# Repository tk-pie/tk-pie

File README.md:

# Tk🥧
Alternatively: **tk-pie**, or **Test Keyboard Please IgnorE**.
A split keyboard design and firmware.

## Directory

### `/lib`
A rust library, and the bulk of the keyboard firmware implementation.
Written using the Embassy framework.

### `/left` and `/right`
Rust binaries, one for each half of the split keyboard.
Most of the actual logic is implemented in `/lib`.

### `/schematic`
KiCad schematics of the keyboard PCBs.

### `/case`
3d-printable files of the keyboard case and related plastics.

### `/editor`
A graphical program for configuring the keyboard layout. Work in progress.

## Compilation target

This Rust workspace contains crates which should be compiled for different targets.
When developing firmware, the target should be set to e.g. `riscv32imac-unknown-none-elf`:

    cargo check --target riscv32imac-unknown-none-elf

And when developing for desktop, the target should be set to your host target.
By default, this is the case. The target can be configured in your editor, or in
`.cargo/config.toml`

## Firmware development

Required tools:
- Rust
- `probe-rs` for flashing the firmware. Follow instructions at https://probe.rs/
- [`flip-link`](https://github.com/knurling-rs/flip-link/)
- A debug probe of some kind, I recommend a [Pitaya-Link](https://github.com/makerdiary/pitaya-link)

To flash:
- plug in the probe,
- `cd` into either `left` or `right`
- `cargo run`

### Running tests
The keyboad library comes with some unit tests:
```
cargo test -p tk-pie --target x86_64-unknown-linux-gnu
```

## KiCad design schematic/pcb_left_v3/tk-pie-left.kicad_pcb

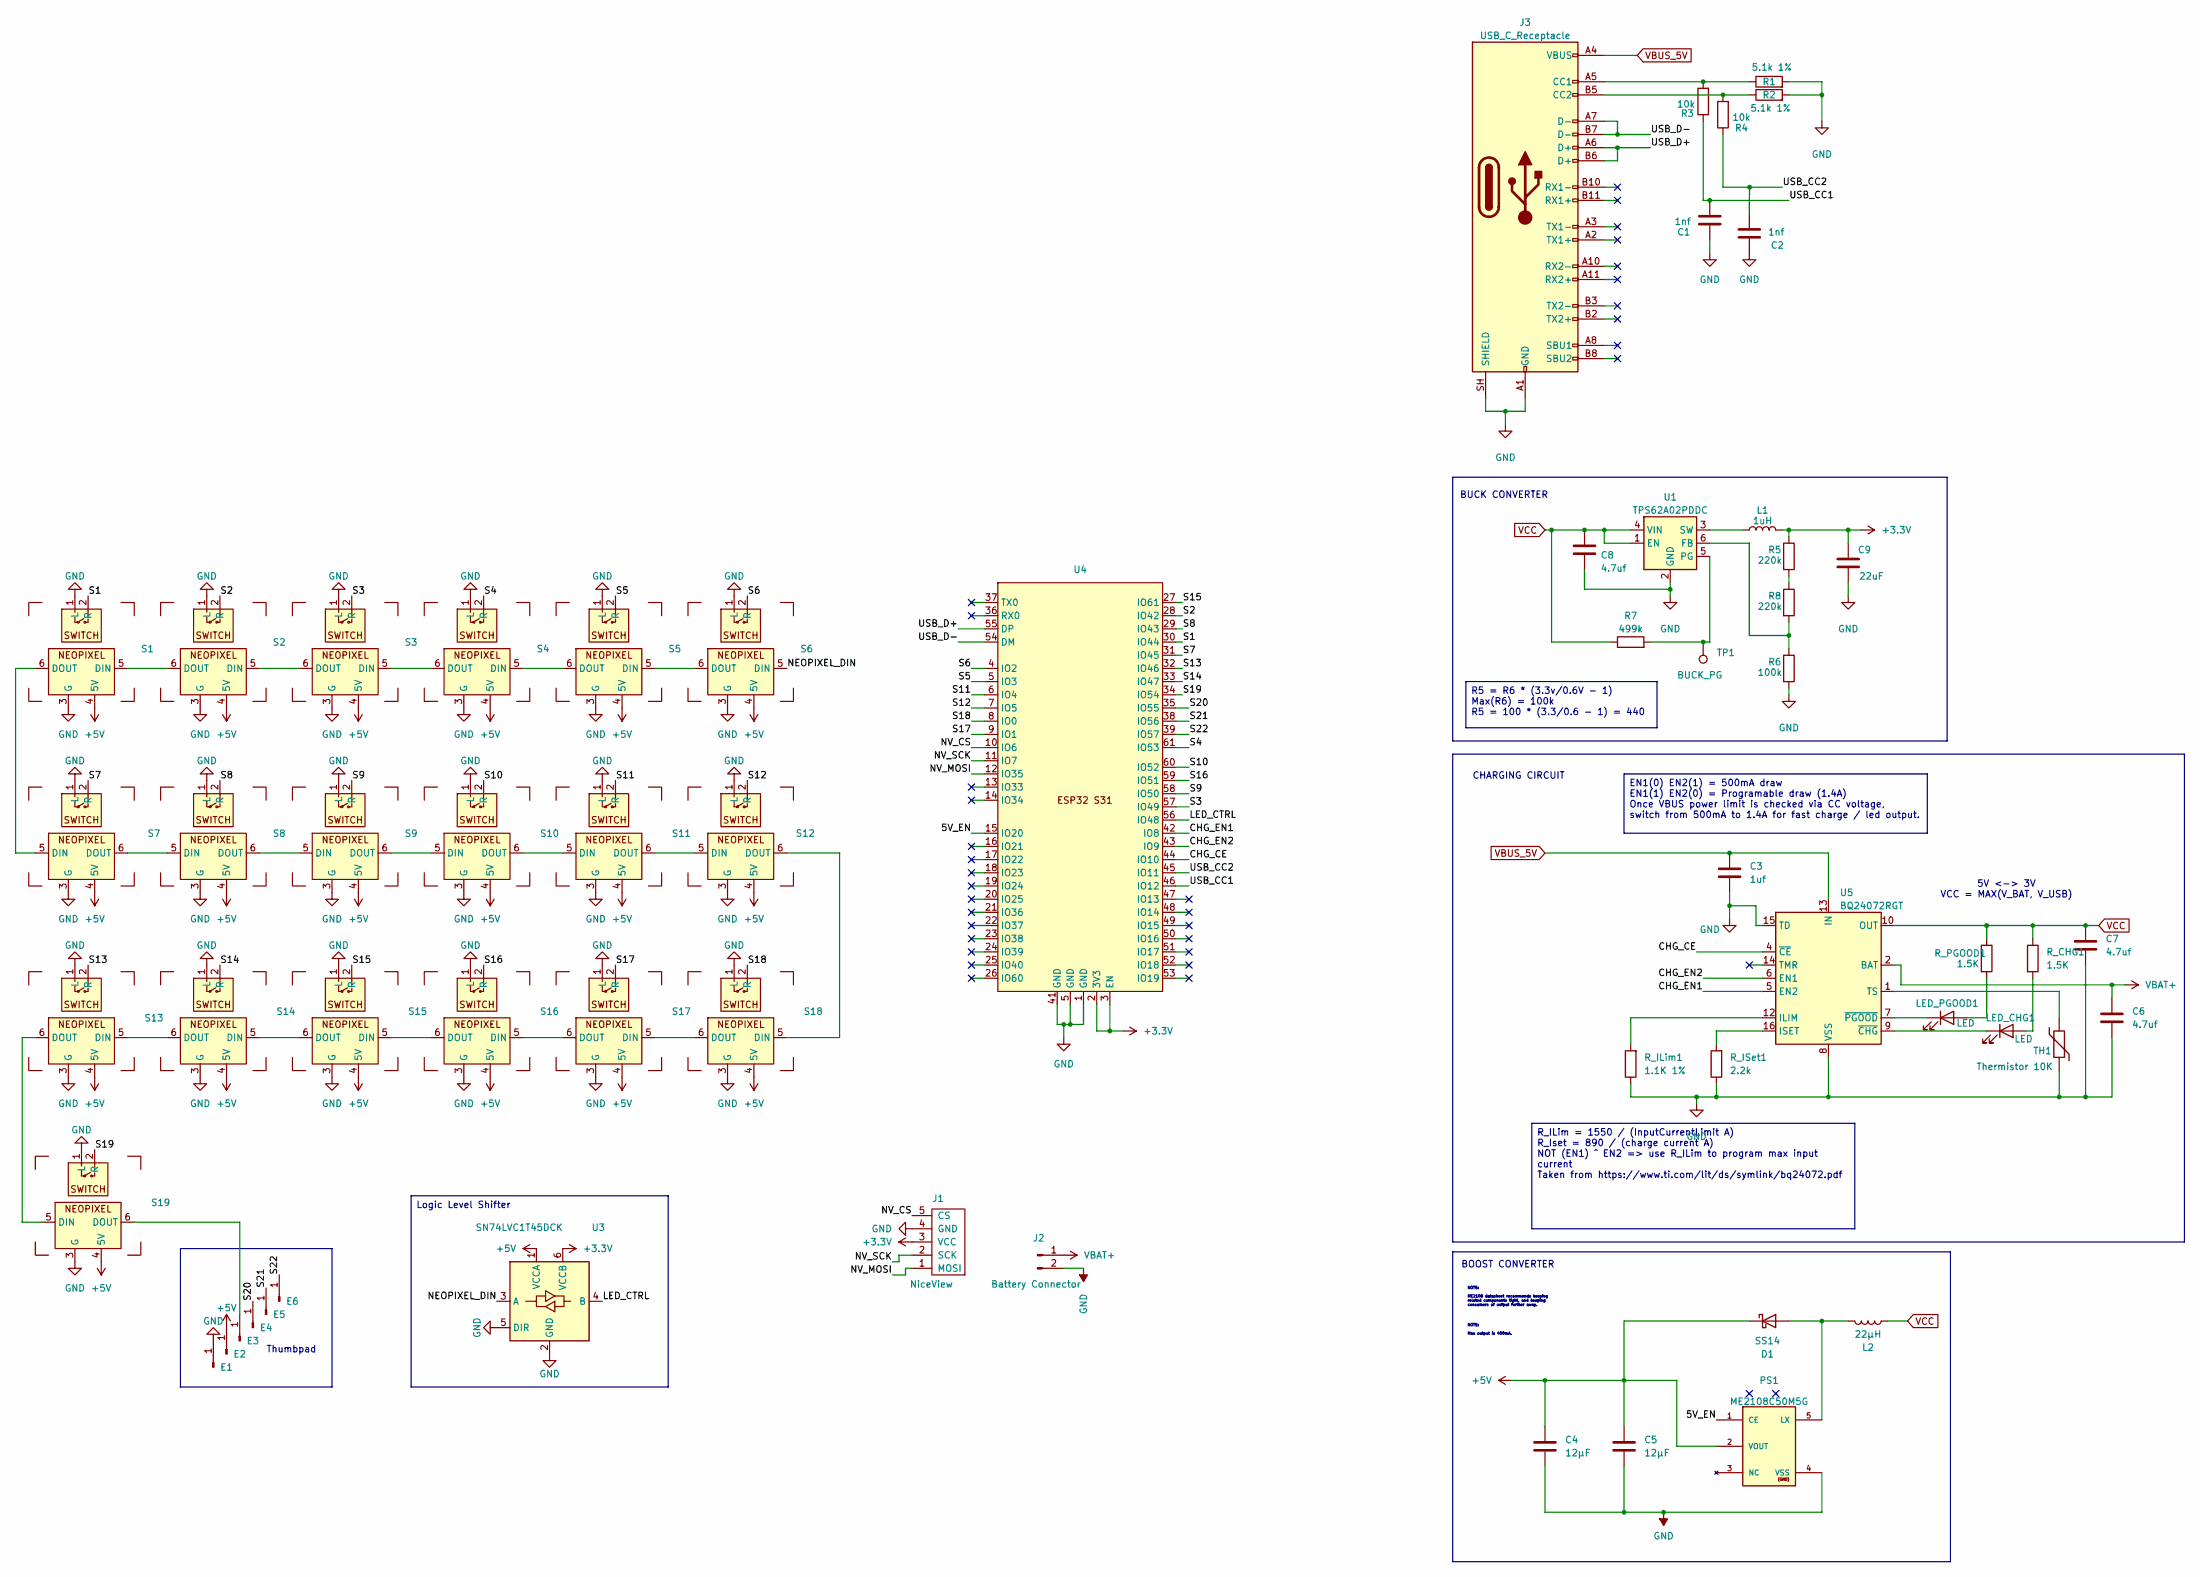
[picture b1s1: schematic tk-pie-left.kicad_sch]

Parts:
C1, C2: 1nf; C_0402_1005Metric_Pad0.74x0.62mm_HandSolder
C3: 1uf; C_0402_1005Metric_Pad0.74x0.62mm_HandSolder
C4, C5: 12µF; C_1210_3225Metric_Pad1.33x2.70mm_HandSolder
C6, C7, C8: 4.7uf; C_0402_1005Metric
C9: 22uF; C_1206_3216Metric
D1: SS14; D_SMA
E1, E2, E3, E4, E5, E6: Conn_01x01_Pin; Pin0.9mm
J1: NiceView; Nice!View Header
J2: Battery Connector; JST_PH_S2B-PH-SM4-TB_1x02-1MP_P2.00mm_Horizontal
J3: USB_C_Receptacle; USB_C_Receptacle_Molex_105450-0101
L1: 1uH; L_1008_2520Metric
L2: 22µH; L_Cenker_CKCS5040
LED_CHG1: LED; LED_0603_1608Metric
LED_PGOOD1: LED; LED_0603_1608Metric
PS1: ME2108C50M5G; SOT-23-5
R1, R2: 5.1k 1%; R_0402_1005Metric
R3, R4: 10k; R_0402_1005Metric
R5, R8: 220k; R_0402_1005Metric
R6: 100k; R_0402_1005Metric
R7: 499k; R_0402_1005Metric
R_CHG1: 1.5K; R_0402_1005Metric
R_ILim1: 1.1K 1%; R_0402_1005Metric
R_ISet1: 2.2k; R_0402_1005Metric
R_PGOOD1: 1.5K; R_0402_1005Metric
S1, S4, S5, S6, S13: MX_SW_SOCKET_LED
S2, S3, S14, S15, S16, S17, S18: MX_SW_SOCKET_LED
S7, S8, S9, S10, S11, S12, S19: MX_SW_SOCKET_RGB_REV; MX_SW_SOCKET_LED_REV
TH1: Thermistor 10K; PinHeader_1x02_P2.54mm_Vertical
TP1: BUCK_PG; TestPoint_Pad_2.5x2.5mm
U1: TPS62A02PDDC; SOT-23-6
U3: SN74LVC1T45DCK; SOT-363_SC-70-6_Handsoldering
U4: ESP32-S31-WROOM-1
U5: BQ24072RGT; VQFN-16-1EP_3x3mm_P0.5mm_EP1.6x1.6mm

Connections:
+3.3V: C9.1, J1.3 (VCC), L1.2, R5.1, U3.6 (VCCB), U4.2 (3V3), U4.3 (EN)
+5V: C4.1, C5.2, D1.1 (K), E2.1 (Pin_1_1), PS1.2 (VOUT), S1.4 (5V), S2.4 (5V), S3.4 (5V), S4.4 (5V), S5.4 (5V), S6.4 (5V), S7.4 (5V), S8.4 (5V), S9.4 (5V), S10.4 (5V), S11.4 (5V), S12.4 (5V), S13.4 (5V), S14.4 (5V), S15.4 (5V), S16.4 (5V), S17.4 (5V), S18.4 (5V), S19.4 (5V), U3.1 (VCCA)
/5V_EN: PS1.1 (CE), U4.15 (IO20)
/ NV_CS: J1.5 (CS), U4.10 (IO6)
/CHG_CE: U4.44 (IO10), U5.4 (~CE)
/CHG_EN1: U4.42 (IO8), U5.5 (EN2)
/CHG_EN2: U4.43 (IO9), U5.6 (EN1)
/LED_CTRL: U3.4 (B), U4.56 (IO48)
/NEOPIXEL_DIN: S6.5 (DIN), U3.3 (A)
/NV_MOSI: J1.1 (MOSI), U4.12 (IO35)
/NV_SCK: J1.2 (SCK), U4.11 (IO7)
/S1: S1.2 (R), U4.30 (IO44)
/S2: S2.2 (R), U4.28 (IO42)
/S3: S3.2 (R), U4.57 (IO49)
/S4: S4.2 (R), U4.61 (IO53)
/S6: S6.2 (R), U4.4 (IO2)
/S7: S7.2 (R), U4.31 (IO45)
/S8: S8.2 (R), U4.29 (IO43)
/S9: S9.2 (R), U4.58 (IO50)
/S10: S10.2 (R), U4.60 (IO52)
/S11: S11.2 (R), U4.6 (IO4)
/S12: S12.2 (R), U4.7 (IO5)
/S13: S13.2 (R), U4.32 (IO46)
/S14: S14.2 (R), U4.33 (IO47)
/S15: S15.2 (R), U4.27 (IO61)
/S16: S16.2 (R), U4.59 (IO51)
/S17: S17.2 (R), U4.9 (IO1)
/S18: S18.2 (R), U4.8 (IO0)
/S19: S19.2 (R), U4.34 (IO54)
/S20: E4.1 (Pin_1_1), U4.35 (IO55)
/S21: E5.1 (Pin_1_1), U4.38 (IO56)
/S22: E6.1 (Pin_1_1), U4.39 (IO57)
/USB_CC1: C1.1, R3.1, U4.46 (IO12)
/USB_CC2: C2.1, R4.1, U4.45 (IO11)
/USB_D+: J3.A6 (D+), J3.B6 (D+), U4.55 (DP)
/USB_D-: J3.A7 (D-), J3.B7 (D-), U4.54 (DM)
unnamed: D1.2 (A), L2.2, PS1.5 (LX)
unnamed: E3.1 (Pin_1_1), S19.6 (DOUT)
unnamed: J3.A5 (CC1), R1.1, R3.2
unnamed: J3.B5 (CC2), R2.1, R4.2
unnamed 40: LED_CHG1.2 (A), R_CHG1.2; also elsewhere on the board
unnamed 41: LED_CHG1.1 (K), U5.9 (~CHG); also elsewhere on the board
unnamed 42: LED_PGOOD1.2 (A), R_PGOOD1.2; also elsewhere on the board
unnamed 43: LED_PGOOD1.1 (K), U5.7 (~PGOOD); also elsewhere on the board
unnamed: R5.2, R8.1
unnamed: S1.5 (DIN), S2.6 (DOUT)
unnamed: S1.6 (DOUT), S7.5 (DIN)
unnamed: S2.5 (DIN), S3.6 (DOUT)
unnamed: S3.5 (DIN), S4.6 (DOUT)
unnamed: S4.5 (DIN), S5.6 (DOUT)
unnamed: S5.5 (DIN), S6.6 (DOUT)
unnamed: S7.6 (DOUT), S8.5 (DIN)
unnamed: S8.6 (DOUT), S9.5 (DIN)
unnamed: S9.6 (DOUT), S10.5 (DIN)
unnamed: S10.6 (DOUT), S11.5 (DIN)
unnamed: S11.6 (DOUT), S12.5 (DIN)
unnamed: S12.6 (DOUT), S18.5 (DIN)
unnamed: S13.5 (DIN), S14.6 (DOUT)
unnamed: S13.6 (DOUT), S19.5 (DIN)
unnamed: S14.5 (DIN), S15.6 (DOUT)
unnamed: S15.5 (DIN), S16.6 (DOUT)
unnamed: S16.5 (DIN), S17.6 (DOUT)
unnamed: S17.5 (DIN), S18.6 (DOUT)
unnamed: R6.1, R8.2, U1.6 (FB)
unnamed: R7.2, TP1.1, U1.5 (PG)
unnamed: L1.1, U1.3 (SW)
unnamed: R_ILim1.2, U5.12 (ILIM)
unnamed: R_ISet1.2, U5.16 (ISET)
unnamed: TH1.2, U5.1 (TS)
VBAT+: C6.1, J2.1, U5.2 (BAT), U5.3 (BAT)
VBUS_5V: C3.1, J3.A4 (VBUS), J3.A9 (VBUS), J3.B4 (VBUS), J3.B9 (VBUS), U5.13 (IN)
VCC: C7.1, C8.1, L2.1, R7.1, R_CHG1.1, R_PGOOD1.1, U1.1 (EN), U1.4 (VIN), U5.10 (OUT), U5.11 (OUT)

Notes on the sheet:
BUCK CONVERTER
CHARGING CIRCUIT
NOTE: Max output is 400mA.
NOTE: ME2108 datasheet recommends keeping related components tight, and keeping consumers of output further away.
5V <-> 3V VCC = MAX(V_BAT, V_USB)
Thumbpad
R_ILim = 1550 / (InputCurrentLimit A) R_Iset = 890 / (charge current A) NOT (EN1) ^ EN2 => use R_ILim to program max input current Taken from https://www.ti.com/lit/ds/symlink/bq24072.pdf
BOOST CONVERTER
EN1(0) EN2(1) = 500mA draw EN1(1) EN2(0) = Programable draw (1.4A) Once VBUS power limit is checked via CC voltage, switch from 500mA to 1.4A for fast charge / led output.
Logic Level Shifter
R5 = R6 * (3.3v/0.6V - 1) Max(R6) = 100k R5 = 100 * (3.3/0.6 - 1) = 440

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
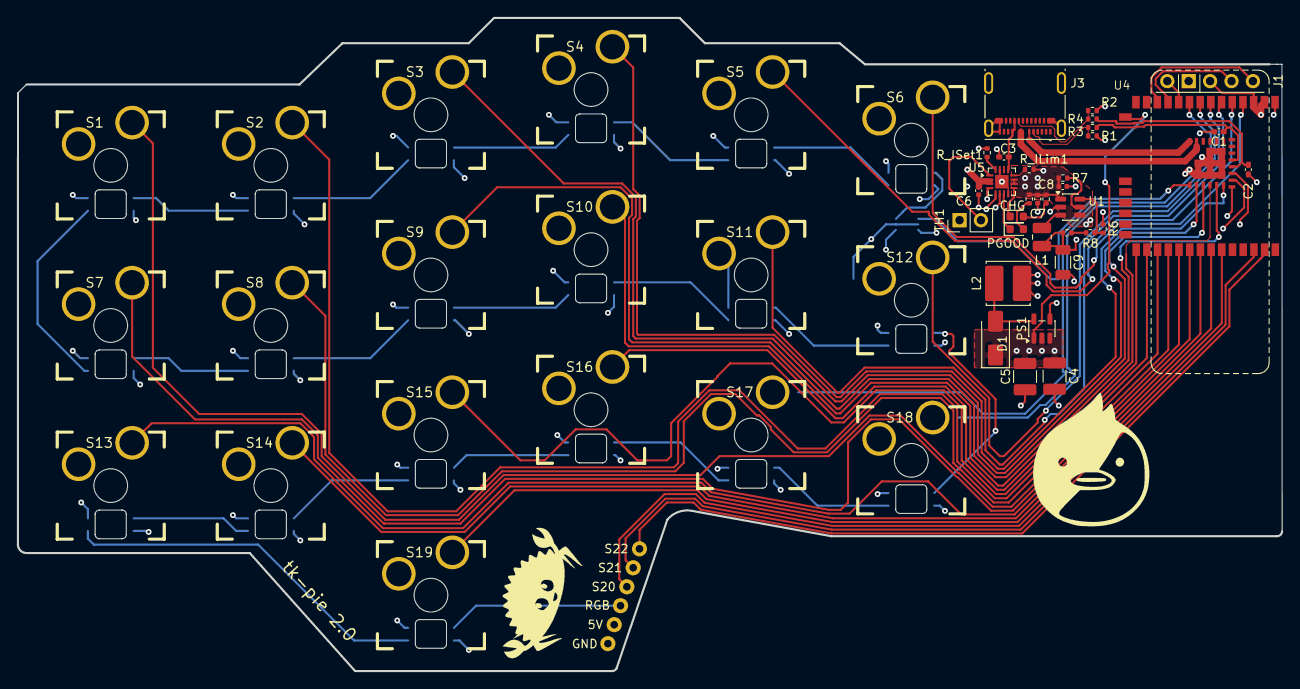
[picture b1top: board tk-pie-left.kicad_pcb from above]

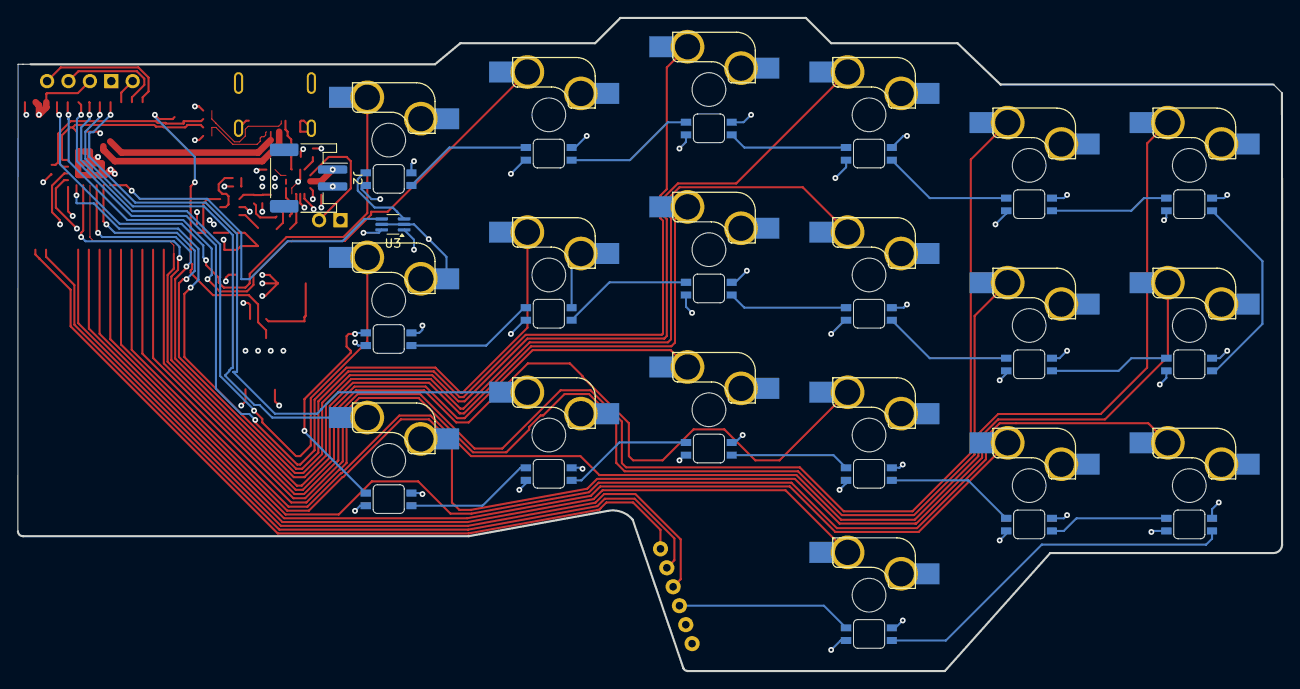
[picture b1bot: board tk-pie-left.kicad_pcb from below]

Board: 4 copper layers, 150.0 x 77.5 mm, 60 parts (2 on the bottom side), 74 nets.

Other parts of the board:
CHG: LED; LED_0603_1608Metric
PGOOD: LED; LED_0603_1608Metric

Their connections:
unnamed 40: CHG.2 (A); also elsewhere on the board
unnamed 41: CHG.1 (K); also elsewhere on the board
unnamed 42: PGOOD.2 (A); also elsewhere on the board
unnamed 43: PGOOD.1 (K); also elsewhere on the board
